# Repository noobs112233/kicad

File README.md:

# Arduino Mega 2560 — KiCad 原理圖繪製練習

對照 `MEGA2560_Rev3e_sch.pdf` 與完整 KiCad 參考專案，使用 **KiCad 9.0** 分工繪製 Arduino Mega 2560 Rev3 原理圖。

---

## Repo 結構

```
kicad/
├── Arduino_Mega2560_Practice/      ← 學生繪製的空白專案（每人畫一個 Section）
│   ├── Arduino_Mega2560_Practice.kicad_pro
│   ├── Arduino_Mega2560_Practice.kicad_sch     (root，4 個子頁框)
│   ├── Section_01_USB_ATmega16U2.kicad_sch     ← 空白
│   ├── Section_02_ATmega2560_MCU.kicad_sch     ← 空白
│   ├── Section_03_Power_Supply.kicad_sch       ← 空白
│   ├── Section_04_Arduino_Headers.kicad_sch    ← 空白
│   ├── Arduino_Mega2560_Lib.kicad_sym          ← 專案符號庫（已預掛 footprint）
│   ├── Arduino_Mega2560_FP.pretty/             ← 自訂 footprint 庫
│   ├── sym-lib-table                           ← 符號庫掛載設定
│   └── fp-lib-table                            ← Footprint 庫掛載設定
│
├── Arduino_Mega2560_Rev3/          ← 完整參考專案（schematic only，無 PCB layout）
│   ├── Arduino Mega 2560.kicad_pro
│   ├── Arduino Mega 2560.kicad_sch             (root)
│   ├── ATMEGA2560-16AU.kicad_sch
│   ├── Power.kicad_sch
│   ├── Headers.kicad_sch
│   ├── Arduino Mega 2560.kicad_sym
│   ├── Arduino Mega 2560.pretty/
│   └── Arduino_Mega2560_Rev3_Schematic.pdf
│
├── PPT/                            ← 課程投影片
├── MEGA2560_Rev3e_sch.pdf          ← 官方參考原理圖
├── arduino_mega2560_BOM.csv        ← 完整 BOM (62 個位號)
└── README.md
```

---

## 分工架構

原理圖分為 **4 個子頁面**，每人負責一個區塊：

| 頁面 | 檔案 | 負責內容 |
|------|------|---------|
| Page 2 | `Section_01_USB_ATmega16U2.kicad_sch` | USB-C 接頭、ESD 保護、ATmega16U2 USB Bridge、晶振 Y2 |
| Page 3 | `Section_02_ATmega2560_MCU.kicad_sch` | ATmega2560 主控 MCU、去耦電容、Reset 電路、晶振 Y1 |
| Page 4 | `Section_03_Power_Supply.kicad_sch` | DC 電源座、NCP1117 5V、LP2985 3.3V、PMOS、LMV358 |
| Page 5 | `Section_04_Arduino_Headers.kicad_sch` | 所有 Arduino 腳位排針（數位/類比/電源） |

---

## 開啟專案

1. 啟動 **KiCad 9.0**
2. `File > Open Project`
3. 選 `Arduino_Mega2560_Practice/Arduino_Mega2560_Practice.kicad_pro`
4. 從 Project Manager 雙擊原理圖開啟 Eeschema
5. 在頁面選擇器切到你負責的 Section 開始繪製

---

## 符號庫 / Footprint 庫使用

### 自動掛載（已設定好，**不需要手動加**）

專案內附的 `sym-lib-table` 與 `fp-lib-table` 已經用 `${KIPRJMOD}` 路徑指向專案資料夾，**只要從 `.kicad_pro` 開啟專案就會自動載入**：

| Library 類型 | 名稱 | 路徑 | 內容 |
|------|------|------|------|
| 符號庫 (Symbol) | `Arduino_Mega2560_Lib` | `Arduino_Mega2560_Lib.kicad_sym` | 92 個符號（ATmega2560、ATmega16U2、被動元件、連接器…） |
| Footprint 庫 | `Arduino_Mega2560_FP` | `Arduino_Mega2560_FP.pretty/` | 4 個自訂 footprint（電源座、針腳、按鍵、Polyfuse） |

> 每個符號已預先連結對應 footprint，**畫原理圖時不需要再指定 footprint**。

### 放置元件

- **Eeschema (原理圖)**: `Place > Add Symbol` (快捷鍵 `A`) → 在 Filter 輸入 `Arduino_Mega2560_Lib:` → 選元件
- **Pcbnew (Footprint)**: `Place > Add Footprint` (快捷鍵 `A`) → Filter 輸入 `Arduino_Mega2560_FP:`

### 看不到符號庫怎麼辦？

如果 Eeschema 找不到 `Arduino_Mega2560_Lib`：

1. `Preferences > Manage Symbol Libraries`
2. 切到 **Project Specific Libraries** 頁籤
3. 確認有一筆 `Arduino_Mega2560_Lib` 指向 `${KIPRJMOD}/Arduino_Mega2560_Lib.kicad_sym`
4. 若無，按 `+` 新增；如果路徑紅字，KiCad 沒讀到專案 → 確認你是用 `.kicad_pro` 開啟，不要直接開 `.kicad_sch`

Footprint 庫同理：`Preferences > Manage Footprint Libraries > Project Specific Libraries`。

---

## 完整參考原理圖

需要對照已完成的版本時，開 `Arduino_Mega2560_Rev3/Arduino Mega 2560.kicad_pro`，含完整 4 頁 schematic。
**此參考專案不附 PCB layout** — layout 要自己畫。

或直接看 PDF：`Arduino_Mega2560_Rev3/Arduino_Mega2560_Rev3_Schematic.pdf`、`MEGA2560_Rev3e_sch.pdf`。

---

## BOM

`arduino_mega2560_BOM.csv` 列出 62 個位號（Reference / Value / Description / Footprint），可以對照確認元件數量與規格。

---

## BOM ↔ 符號庫 對照表

> ⚠️ 符號庫的命名不統一 — 有些用「料號」(`ATmega2560_16AU`)、有些用「通用封裝名」(`Fuse_1812`、`C_SMD_0603`)。直接搜料號常常找不到，請對照下表搜尋：

### 被動元件
| BOM Ref | 元件 | **在符號庫搜這個名字** |
|---|---|---|
| C1–C16 | 0603 SMD 電容 | `C_SMD_0603` |
| PC1, PC2 | 47µF 鋁電解 (THT) | `C_Pol` |
| R1, R2 | 0603 SMD 電阻 | `R_SMD_0603` |
| RN1–RN5 | SIP8 排阻 | `RArray_4x0612` |
| L1 | Ferrite bead 0805 | `FerriteBead_0805` |
| **F1** | **PPTC182LFBN-RC Polyfuse 1812** | **`Fuse_1812`** ← 不是料號！ |

### 主動元件
| BOM Ref | 元件 | **搜這個名字** |
|---|---|---|
| IC1 | LD1117 5V LDO (SOT-223) | `NCP1117_5_0_SOT223` ⚠️ 符號名是 NCP1117，pin out 相容 |
| IC3 | ATmega2560 | `ATmega2560_16AU` |
| IC4 | ATmega16U2 | `ATmega16U2_MU` |
| IC6 | LP2985 3.3V LDO | `LP2985_3_3` |
| IC7 | LMV358 op-amp | `LMV358` |
| T1 | PMV48XP P-MOSFET | `Q_PMOS_GSD` |
| D1 | M7 整流二極體 (SMB) | `D_SMB` |
| D2, D3 | CD1206 高速二極體 | `D_1206` |
| Z1, Z2 | 0603 ESD Varistor | `Varistor_0603` |

### 振盪器 / 開關 / LED
| BOM Ref | 元件 | **搜這個名字** |
|---|---|---|
| Y1 | CSTCE16M0V53-R0 三腳陶瓷諧振器 | `Resonator_3Pin` |
| Y2 | 16MHz HC-49/S 晶振 | `Crystal_HC49` |
| RESET | TS42 Tactile 按鍵 | `SW_Reset` |
| ON / L / RX / TX | 0805 LED | `LED_0805` |

### 連接器
| BOM Ref | 元件 | **搜這個名字** |
|---|---|---|
| X1 | DC 電源座 2.1mm | `Barrel_Jack_Switch` |
| X2 | USB Type-B (BOM) ※ 符號庫實作為 USB-C | `USB_C_16P` ⚠️ 與 BOM 不一致，依 Rev3e 改為 USB-C |
| ICSP, ICSP1 | 2x3 排針 | `Header_2x03` |
| JP5 | 2x2 排針 | `Header_2x02` |
| JP6 | 1x10 排母 | `Conn_01x10` |
| POWER, ADCH, ADCL, COMMUNICATION, PWML | 1x8 排母 | `Conn_01x08` |
| XIO | 2x18 排母 | `Conn_02x18_Odd_Even` |

### 雜項
| BOM Ref | 元件 | **搜這個名字** |
|---|---|---|
| GROUND, RESET-EN | Solder jumper | `SolderJumper_2` |
| FD1–FD4 | Fiducial | `Fiducial_1mm` |

### 電源符號（不在 BOM，畫線時需要）
| 用途 | 名稱 |
|---|---|
| 5V 電源 | `PWR_5V` |
| 3.3V 電源 | `PWR_3V3` |
| GND | `PWR_GND` |
| VCC（USB 5V） | `VCC` |

### 搜尋技巧
1. 在 Eeschema 按 `A` 開啟 Add Symbol
2. 上方 Filter 輸入 `Arduino_Mega2560_Lib:` 只看本專案符號庫（共 31 個符號）
3. 從上表查到名字後直接搜（例如要 Polyfuse 就搜 `Fuse_1812`）

---

## Git 協作流程

### 初始設定

```bash
# 1. 先 fork 這個 repo 到你們組的帳號
# 2. Clone 到本機
git clone https://github.com/<你的組別>/kicad.git
cd kicad
```

### 每個人的工作流程

```bash
# 建立自己的 branch（以你負責的區塊命名）
git checkout -b section/01-usb-atmega16u2   # 依你的區塊修改

# 繪製原理圖後，只 commit 你負責的那個 .kicad_sch 檔
git add Arduino_Mega2560_Practice/Section_01_USB_ATmega16U2.kicad_sch
git commit -m "feat: complete USB ATmega16U2 section schematic"

# Push 到遠端
git push origin section/01-usb-atmega16u2

# 在 GitHub 發 Pull Request 給你們組的 main branch
```

### 合併注意事項

- 每個人只修改**自己負責的 `.kicad_sch` 檔**，不要動到其他人的檔案
- Root 主頁面 `Arduino_Mega2560_Practice.kicad_sch` 只有 4 個方框，不需要修改
- **不要 commit `.kicad_pcb`**（已被 `.gitignore` 排除），這個練習只做原理圖
- `*.bak`、`*.kicad_prl`、`*-backups/` 也都已被 ignore
- 合併後在 KiCad 開 `Arduino_Mega2560_Practice.kicad_pro` 即可看到完整原理圖

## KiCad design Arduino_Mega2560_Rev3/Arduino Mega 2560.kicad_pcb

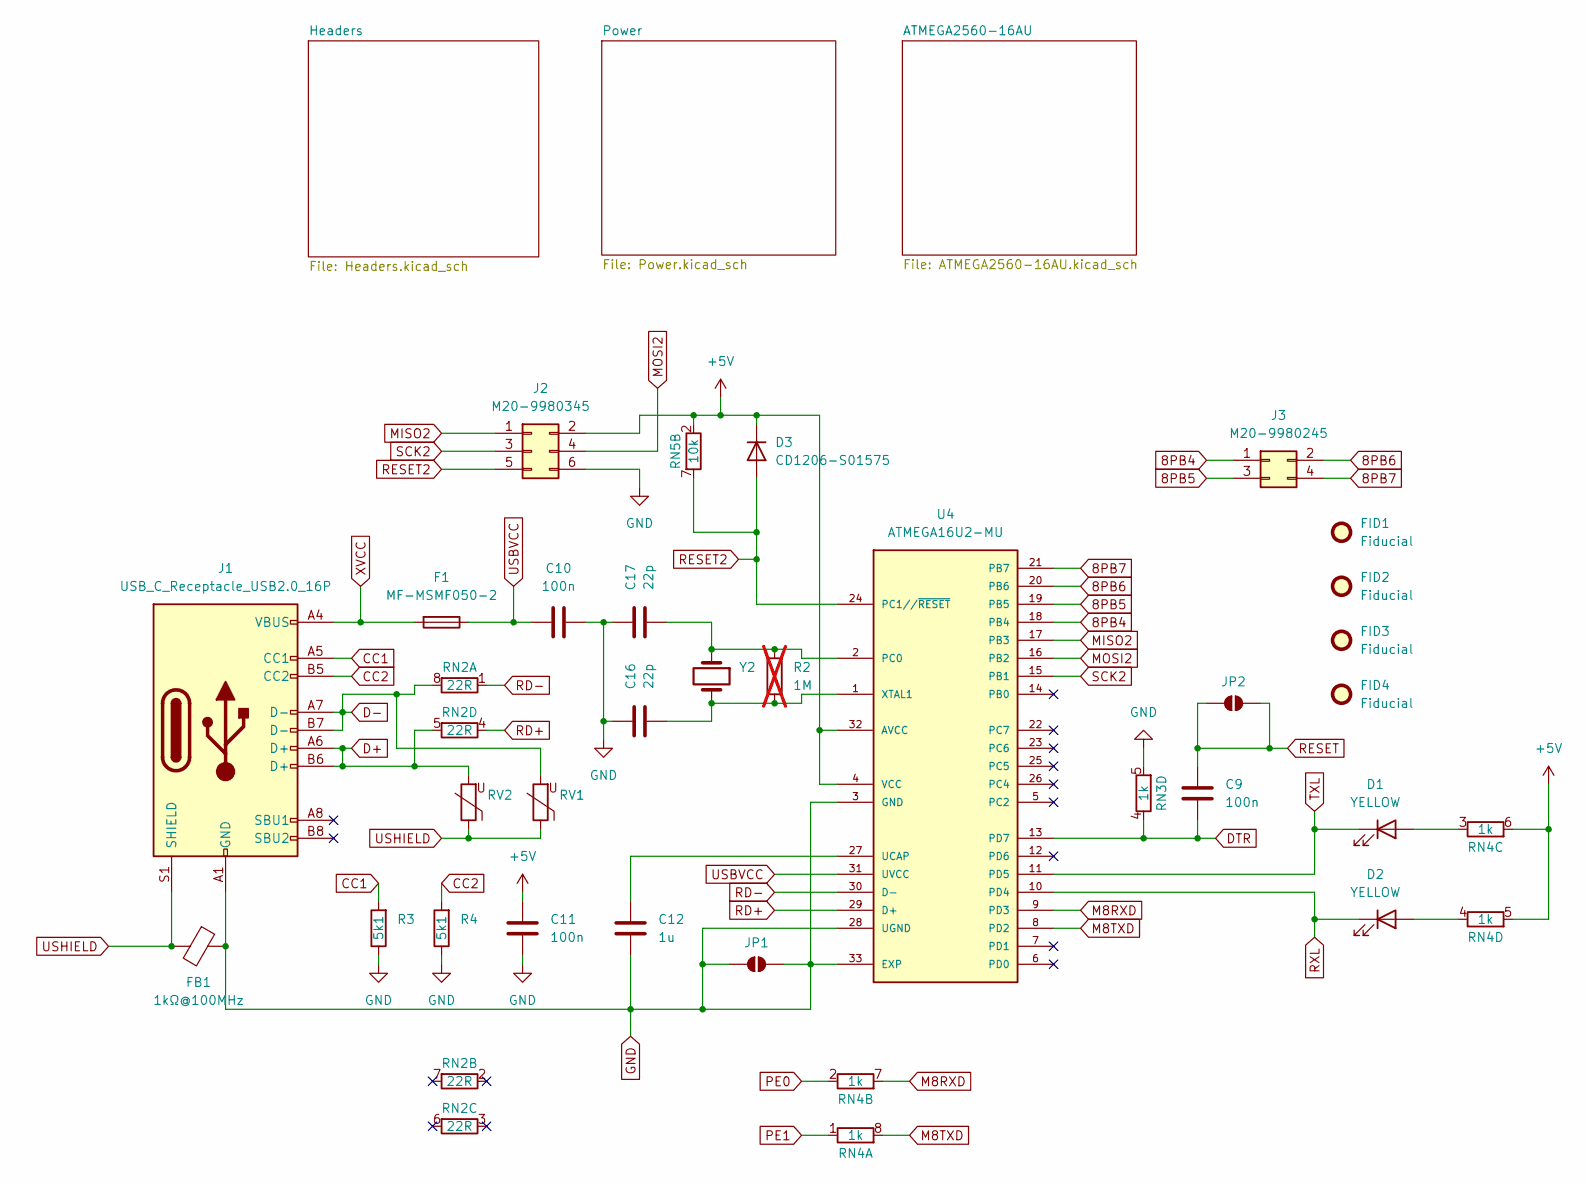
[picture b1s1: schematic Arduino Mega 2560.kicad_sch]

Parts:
C9, C10, C11: 100n; C_0603_1608Metric
C12: 1u; C_0603_1608Metric
C16, C17: 22p; C_0603_1608Metric
D1, D2: YELLOW; LED_0805_2012Metric
D3: CD1206-S01575; D_1206_3216Metric
F1: MF-MSMF050-2; Fuse_1812_4532Metric_Pad1.30x3.40mm_HandSolder
FB1: 1kΩ@100MHz; L_0805_2012Metric
FID1, FID2, FID3, FID4: Fiducial; Fiducial_1mm_Mask3mm
J1: USB_C_Receptacle_USB2.0_16P; USB_C_Receptacle_GCT_USB4105-xx-A_16P_TopMnt_Horizontal
J2: M20-9980345; PinHeader_2x03_P2.54mm_Vertical
J3: M20-9980245; CONN_M20-9980245_HRW
JP1, JP2: SolderJumper_2_Open; SolderJumper-2_P1.3mm_Open_Pad1.0x1.5mm
R2: 1M; R_0603_1608Metric; not fitted
R3, R4: 5k1; R_0603_1608Metric
RN2: 22R; R_Array_Convex_4x0612
RN3, RN4: 1k; R_Array_Convex_4x0612
RN5: 10k; R_Array_Convex_4x0612
RV1, RV2: 5pF@1MHz; R_0603_1608Metric
U4: ATMEGA16U2-MU; VQFN-32-1EP_5x5mm_P0.5mm_EP3.1x3.1mm
Y2: LFXTAL003240BULK; Crystal_HC49-4H_Vertical

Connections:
8PB4: J3.1, U4.18 (PB4)
8PB5: J3.3, U4.19 (PB5)
8PB6: J3.2, U4.20 (PB6)
8PB7: J3.4, U4.21 (PB7)
+5V: C11.1, D3.1 (K), J2.2, RN4.5 (R4.2), RN4.6 (R3.2), RN5.2 (R2.1), U4.4 (VCC), U4.32 (AVCC); also elsewhere on the board
CC1: J1.A5 (CC1), R3.2
CC2: J1.B5 (CC2), R4.2
D+: J1.A6 (D+), J1.B6 (D+), RN2.5 (R4.2), RV2.2
D-: J1.A7 (D-), J1.B7 (D-), RN2.8 (R1.2), RV1.2
DTR: C9.1, RN3.4 (R4.1), U4.13 (PD7)
GND: C10.2, C11.2, C12.2, C16.2, C17.2, FB1.1, J1.A1 (GND), J1.A12 (GND), J1.B1 (GND), J1.B12 (GND), J2.6, JP1.1 (A), JP1.2 (B), R3.1, R4.1, RN3.5 (R4.2), U4.3 (GND), U4.28 (UGND), U4.33 (EXP); also elsewhere on the board
M8RXD: RN4.7 (R2.2), U4.9 (PD3)
M8TXD: RN4.8 (R1.2), U4.8 (PD2)
MISO2: J2.1, U4.17 (PB3)
MOSI2: J2.4, U4.16 (PB2)
unnamed: D1.2 (A), RN4.3 (R3.1)
unnamed: D2.2 (A), RN4.4 (R4.1)
unnamed: C17.1, R2.2, U4.2 (PC0), Y2.1
unnamed: C12.1, U4.27 (UCAP)
unnamed: C16.1, R2.1, U4.1 (XTAL1), Y2.2
PE0: RN4.2 (R2.1); also elsewhere on the board
PE1: RN4.1 (R1.1); also elsewhere on the board
RD+: RN2.4 (R4.1), U4.29 (D+)
RD-: RN2.1 (R1.1), U4.30 (D-)
RESET: C9.2, JP2.1 (A), JP2.2 (B); also elsewhere on the board
RESET2: D3.2 (A), J2.5, RN5.7 (R2.2), U4.24 (PC1//~RESET)
RXL: D2.1 (K), U4.10 (PD4)
SCK2: J2.3, U4.15 (PB1)
TXL: D1.1 (K), U4.11 (PD5)
USBVCC: C10.1, F1.1, U4.31 (UVCC); also elsewhere on the board
USHIELD: FB1.2, J1.S1 (SHIELD), RV1.1, RV2.1
XVCC: F1.2, J1.A4 (VBUS), J1.A9 (VBUS), J1.B4 (VBUS), J1.B9 (VBUS)

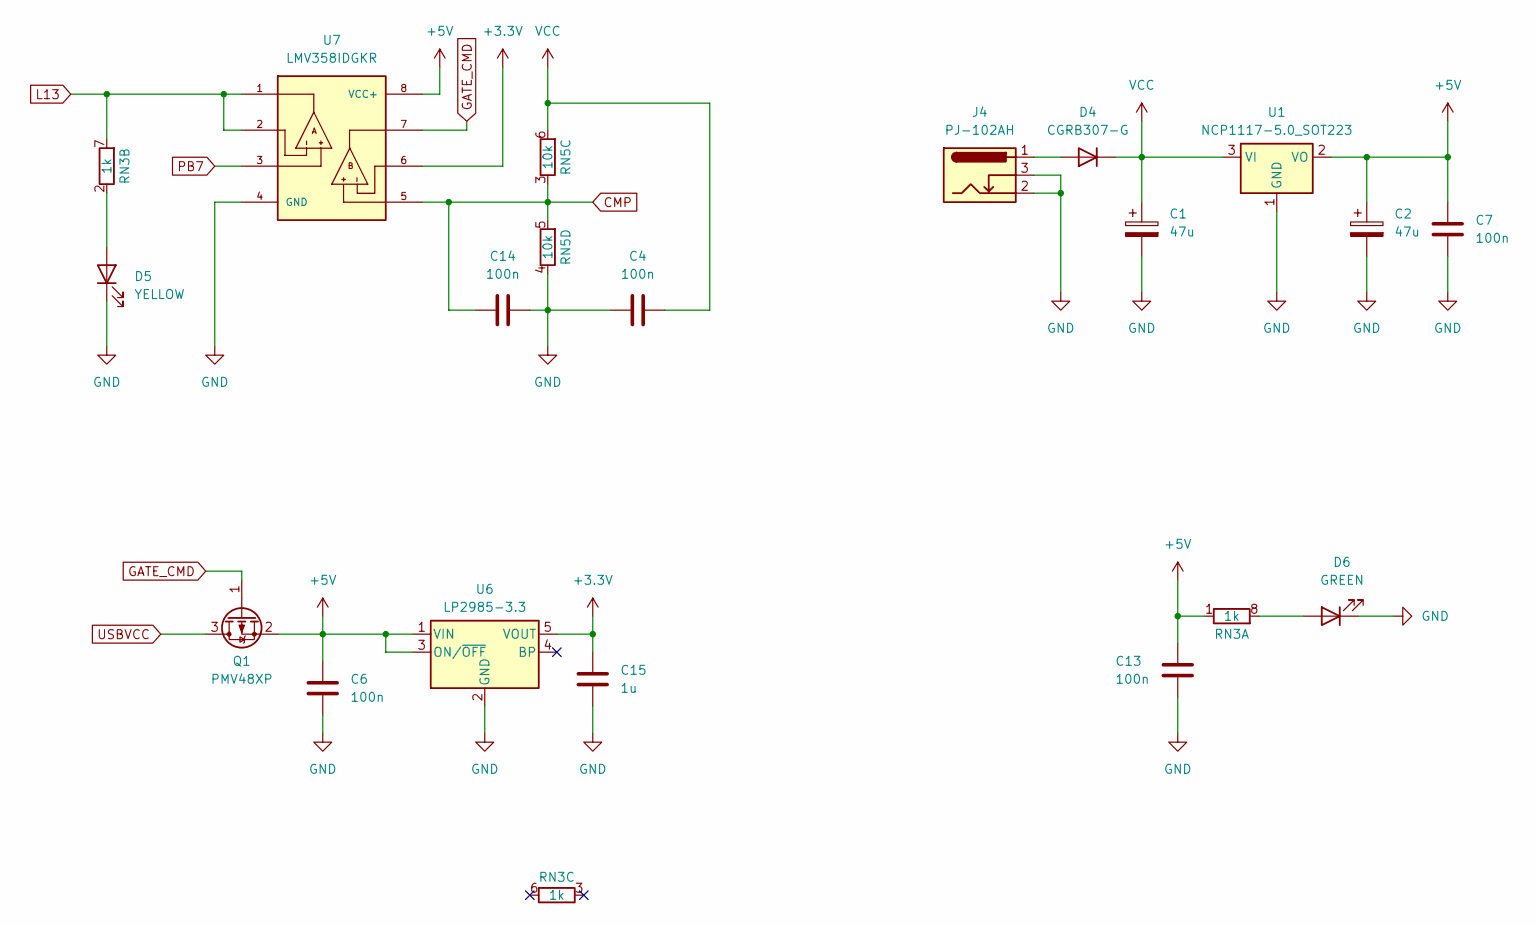
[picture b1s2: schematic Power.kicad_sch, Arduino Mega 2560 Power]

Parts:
C1, C2: 47u; CAP_EEHZA1E470P
C4, C6, C7, C13, C14: 100n; C_0603_1608Metric
C15: 1u; C_0603_1608Metric
D4: CGRB307-G; D_SMB
D5: YELLOW; LED_0805_2012Metric
D6: GREEN; LED_0805_2012Metric
J4: PJ-102AH; BarrelJack_Kycon_KLDX-0202-xC_Horizontal
Q1: PMV48XP; SC-59
RN3: 1k; R_Array_Convex_4x0612
RN5: 10k; R_Array_Convex_4x0612
U1: NCP1117-5.0_SOT223; SOT-223-3_TabPin2
U6: LP2985-3.3; SOT-23-5
U7: LMV358IDGKR; MSOP-8_3x3mm_P0.65mm; PARTREV X

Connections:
+3.3V: C15.2, U6.5 (VOUT), U7.6; also elsewhere on the board
+5V: C2.1, C6.1, C7.1, C13.2, Q1.2 (S), RN3.1 (R1.1), U1.2 (VO), U6.1 (VIN), U6.3 (ON/~OFF), U7.8 (VCC+); also elsewhere on the board
CMP: C14.2, RN5.3 (R3.1), RN5.5 (R4.2), U7.5
GATE_CMD: Q1.1 (G), U7.7
GND: C1.2, C2.2, C4.2, C6.2, C7.2, C13.1, C14.1, C15.1, D5.1 (K), D6.1 (K), J4.2, J4.3, RN5.4 (R4.1), U1.1 (GND), U6.2 (GND), U7.4 (GND); also elsewhere on the board
L13: RN3.7 (R2.2), U7.1, U7.2
unnamed: D4.2 (A), J4.1
unnamed: D5.2 (A), RN3.2 (R2.1)
unnamed: D6.2 (A), RN3.8 (R1.2)
PB7: U7.3; also elsewhere on the board
USBVCC: Q1.3 (D); also elsewhere on the board
VCC: C1.1, C4.1, D4.1 (K), RN5.6 (R3.2), U1.3 (VI); also elsewhere on the board

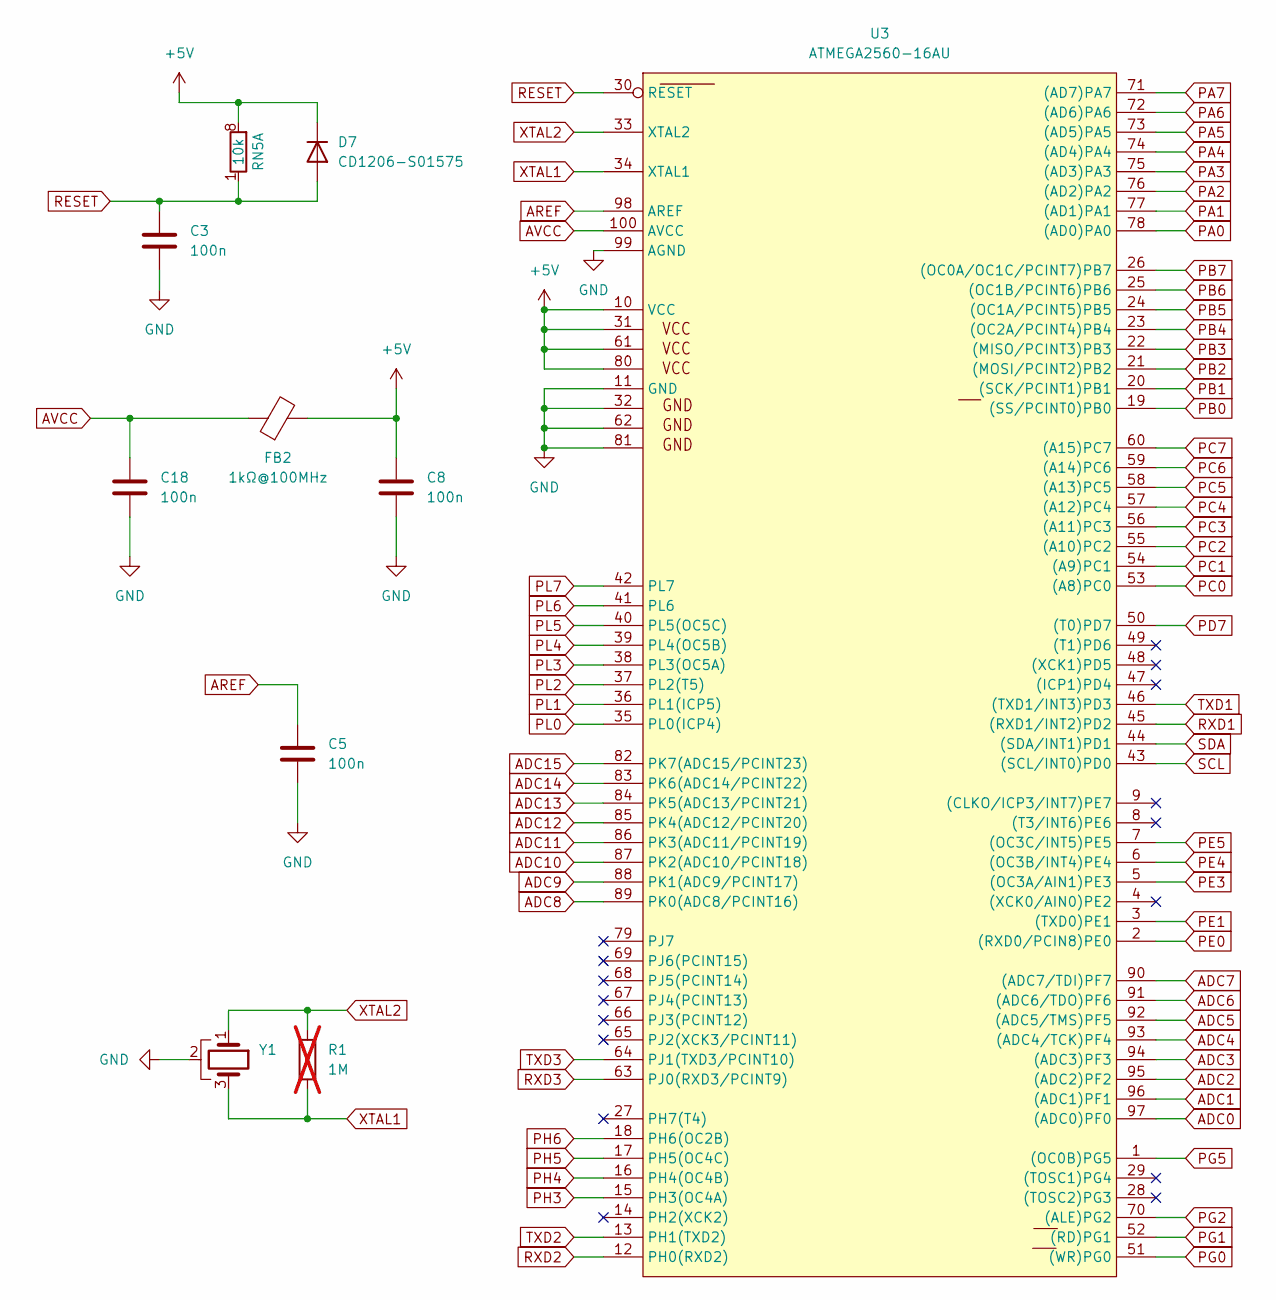
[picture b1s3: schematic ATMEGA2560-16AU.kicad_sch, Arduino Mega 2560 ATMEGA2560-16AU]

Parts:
C3, C5, C8, C18: 100n; C_0603_1608Metric
D7: CD1206-S01575; D_1206_3216Metric
FB2: 1kΩ@100MHz; L_0805_2012Metric
R1: 1M; R_0603_1608Metric; not fitted
RN5: 10k; R_Array_Convex_4x0612
U3: ATMEGA2560-16AU; TQFP-100_14x14mm_P0.5mm
Y1: CSTNE16M0V530000R0; Resonator_SMD_Murata_CSTxExxV-3Pin_3.0x1.1mm

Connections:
+5V: C8.1, D7.1 (K), FB2.2, RN5.8 (R1.2), U3.10 (VCC), U3.31 (VCC1), U3.61 (VCC2), U3.80 (VCC3); also elsewhere on the board
ADC0: U3.97 ((ADC0)PF0); also elsewhere on the board
ADC1: U3.96 ((ADC1)PF1); also elsewhere on the board
ADC2: U3.95 ((ADC2)PF2); also elsewhere on the board
ADC3: U3.94 ((ADC3)PF3); also elsewhere on the board
ADC4: U3.93 ((ADC4/TCK)PF4); also elsewhere on the board
ADC5: U3.92 ((ADC5/TMS)PF5); also elsewhere on the board
ADC6: U3.91 ((ADC6/TDO)PF6); also elsewhere on the board
ADC7: U3.90 ((ADC7/TDI)PF7); also elsewhere on the board
ADC8: U3.89 (PK0(ADC8/PCINT16)); also elsewhere on the board
ADC9: U3.88 (PK1(ADC9/PCINT17)); also elsewhere on the board
ADC10: U3.87 (PK2(ADC10/PCINT18)); also elsewhere on the board
ADC11: U3.86 (PK3(ADC11/PCINT19)); also elsewhere on the board
ADC12: U3.85 (PK4(ADC12/PCINT20)); also elsewhere on the board
ADC13: U3.84 (PK5(ADC13/PCINT21)); also elsewhere on the board
ADC14: U3.83 (PK6(ADC14/PCINT22)); also elsewhere on the board
ADC15: U3.82 (PK7(ADC15/PCINT23)); also elsewhere on the board
AREF: C5.1, U3.98 (AREF); also elsewhere on the board
AVCC: C18.1, FB2.1, U3.100 (AVCC)
GND: C3.2, C5.2, C8.2, C18.2, U3.11 (GND), U3.32 (GND1), U3.62 (GND2), U3.81 (GND3), U3.99 (AGND), Y1.2; also elsewhere on the board
PA0: U3.78 ((AD0)PA0); also elsewhere on the board
PA1: U3.77 ((AD1)PA1); also elsewhere on the board
PA2: U3.76 ((AD2)PA2); also elsewhere on the board
PA3: U3.75 ((AD3)PA3); also elsewhere on the board
PA4: U3.74 ((AD4)PA4); also elsewhere on the board
PA5: U3.73 ((AD5)PA5); also elsewhere on the board
PA6: U3.72 ((AD6)PA6); also elsewhere on the board
PA7: U3.71 ((AD7)PA7); also elsewhere on the board
PB0: U3.19 ((SS/PCINT0)PB0); also elsewhere on the board
PB1: U3.20 ((SCK/PCINT1)PB1); also elsewhere on the board
PB2: U3.21 ((MOSI/PCINT2)PB2); also elsewhere on the board
PB3: U3.22 ((MISO/PCINT3)PB3); also elsewhere on the board
PB4: U3.23 ((OC2A/PCINT4)PB4); also elsewhere on the board
PB5: U3.24 ((OC1A/PCINT5)PB5); also elsewhere on the board
PB6: U3.25 ((OC1B/PCINT6)PB6); also elsewhere on the board
PB7: U3.26 ((OC0A/OC1C/PCINT7)PB7); also elsewhere on the board
PC0: U3.53 ((A8)PC0); also elsewhere on the board
PC1: U3.54 ((A9)PC1); also elsewhere on the board
PC2: U3.55 ((A10)PC2); also elsewhere on the board
PC3: U3.56 ((A11)PC3); also elsewhere on the board
PC4: U3.57 ((A12)PC4); also elsewhere on the board
PC5: U3.58 ((A13)PC5); also elsewhere on the board
PC6: U3.59 ((A14)PC6); also elsewhere on the board
PC7: U3.60 ((A15)PC7); also elsewhere on the board
PD7: U3.50 ((T0)PD7); also elsewhere on the board
PE0: U3.2 ((RXD0/PCIN8)PE0); also elsewhere on the board
PE1: U3.3 ((TXD0)PE1); also elsewhere on the board
PE3: U3.5 ((OC3A/AIN1)PE3); also elsewhere on the board
PE4: U3.6 ((OC3B/INT4)PE4); also elsewhere on the board
PE5: U3.7 ((OC3C/INT5)PE5); also elsewhere on the board
PG0: U3.51 ((WR)PG0); also elsewhere on the board
PG1: U3.52 ((RD)PG1); also elsewhere on the board
PG2: U3.70 ((ALE)PG2); also elsewhere on the board
PG5: U3.1 ((OC0B)PG5); also elsewhere on the board
PH3: U3.15 (PH3(OC4A)); also elsewhere on the board
PH4: U3.16 (PH4(OC4B)); also elsewhere on the board
PH5: U3.17 (PH5(OC4C)); also elsewhere on the board
PH6: U3.18 (PH6(OC2B)); also elsewhere on the board
PL0: U3.35 (PL0(ICP4)); also elsewhere on the board
PL1: U3.36 (PL1(ICP5)); also elsewhere on the board
PL2: U3.37 (PL2(T5)); also elsewhere on the board
PL3: U3.38 (PL3(OC5A)); also elsewhere on the board
PL4: U3.39 (PL4(OC5B)); also elsewhere on the board
PL5: U3.40 (PL5(OC5C)); also elsewhere on the board
PL6: U3.41 (PL6); also elsewhere on the board
PL7: U3.42 (PL7); also elsewhere on the board
RESET: C3.1, D7.2 (A), RN5.1 (R1.1), U3.30 (RESET); also elsewhere on the board
RXD1: U3.45 ((RXD1/INT2)PD2); also elsewhere on the board
RXD2: U3.12 (PH0(RXD2)); also elsewhere on the board
RXD3: U3.63 (PJ0(RXD3/PCINT9)); also elsewhere on the board
SCL: U3.43 ((SCL/INT0)PD0); also elsewhere on the board
SDA: U3.44 ((SDA/INT1)PD1); also elsewhere on the board
TXD1: U3.46 ((TXD1/INT3)PD3); also elsewhere on the board
TXD2: U3.13 (PH1(TXD2)); also elsewhere on the board
TXD3: U3.64 (PJ1(TXD3/PCINT10)); also elsewhere on the board
XTAL1: R1.1, U3.34 (XTAL1), Y1.3
XTAL2: R1.2, U3.33 (XTAL2), Y1.1

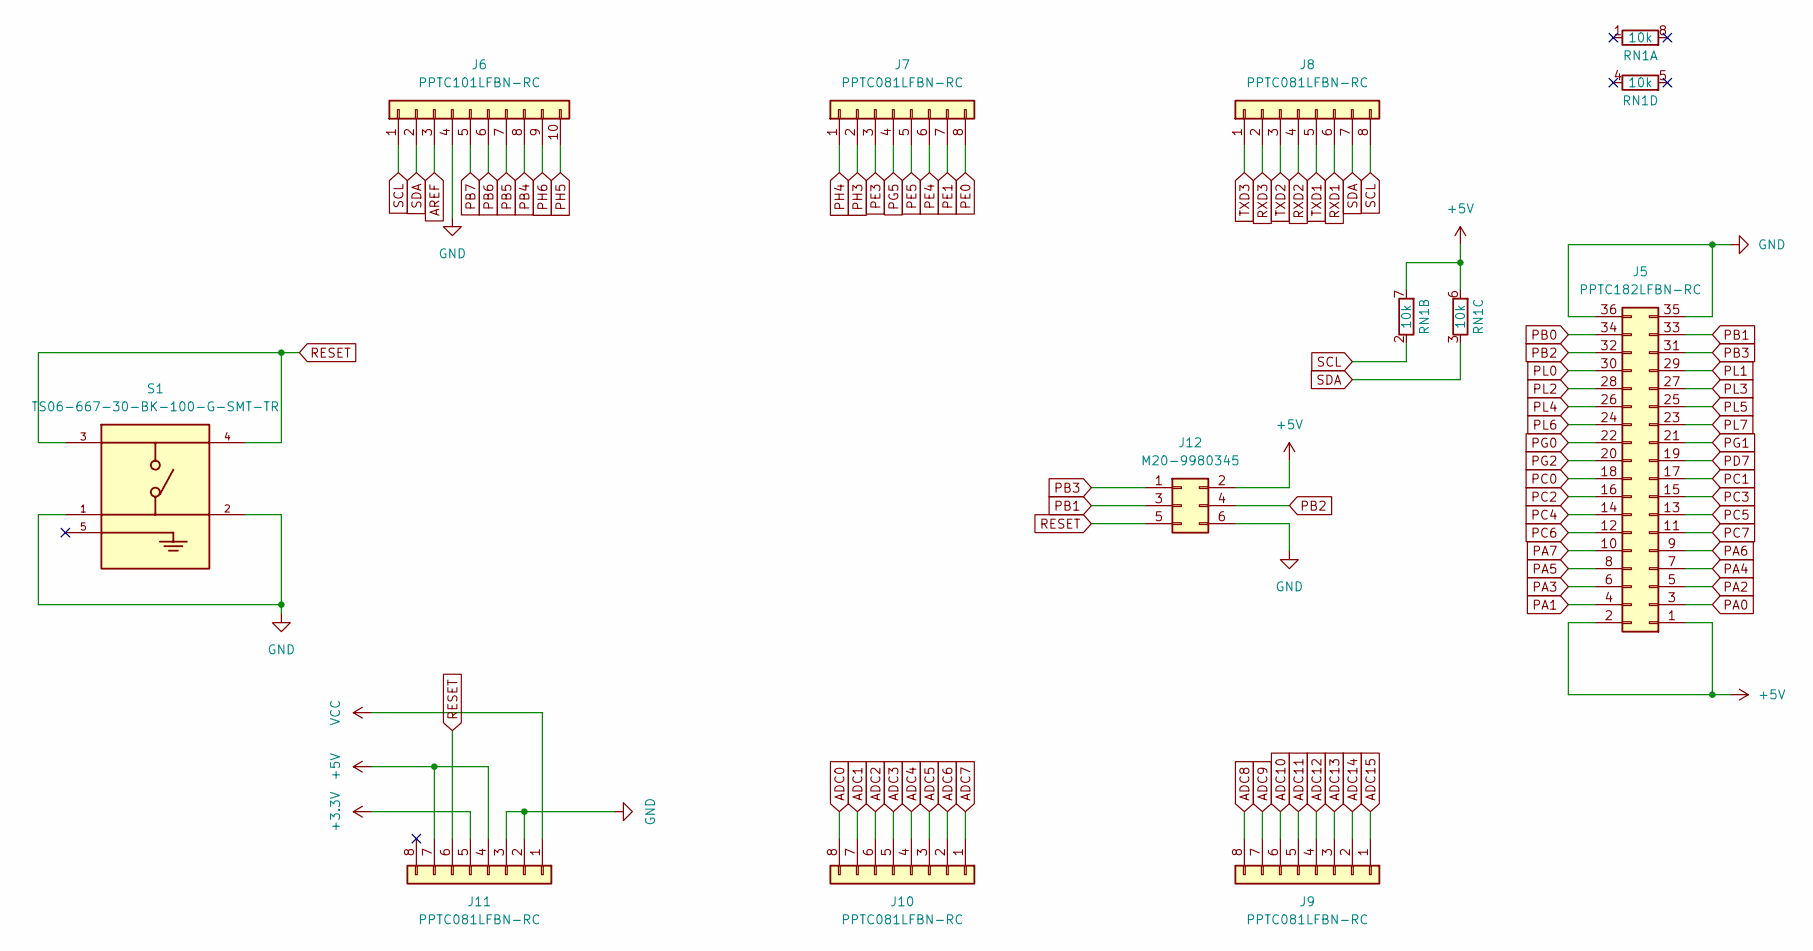
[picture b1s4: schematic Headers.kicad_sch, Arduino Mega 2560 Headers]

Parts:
J5: PPTC182LFBN-RC
J6: PPTC101LFBN-RC; PinSocket_1x10_P2.54mm_Vertical
J7, J8, J9, J10, J11: PPTC081LFBN-RC; PinSocket_1x08_P2.54mm_Vertical
J12: M20-9980345; PinHeader_2x03_P2.54mm_Vertical
RN1: 10k; R_Array_Convex_4x0612
S1: TS06-667-30-BK-100-G-SMT-TR; SW_TS06-667-30-BK-100-G-SMT-TR; PARTREV 1.0

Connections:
+3.3V: J11.5; also elsewhere on the board
+5V: J5.1, J5.2, J11.4, J11.7, J12.2, RN1.6 (R3.2), RN1.7 (R2.2); also elsewhere on the board
ADC0: J10.8; also elsewhere on the board
ADC1: J10.7; also elsewhere on the board
ADC2: J10.6; also elsewhere on the board
ADC3: J10.5; also elsewhere on the board
ADC4: J10.4; also elsewhere on the board
ADC5: J10.3; also elsewhere on the board
ADC6: J10.2; also elsewhere on the board
ADC7: J10.1; also elsewhere on the board
ADC8: J9.8; also elsewhere on the board
ADC9: J9.7; also elsewhere on the board
ADC10: J9.6; also elsewhere on the board
ADC11: J9.5; also elsewhere on the board
ADC12: J9.4; also elsewhere on the board
ADC13: J9.3; also elsewhere on the board
ADC14: J9.2; also elsewhere on the board
ADC15: J9.1; also elsewhere on the board
AREF: J6.3; also elsewhere on the board
GND: J5.35, J5.36, J6.4, J11.2, J11.3, J12.6, S1.1, S1.2; also elsewhere on the board
PA0: J5.3; also elsewhere on the board
PA1: J5.4; also elsewhere on the board
PA2: J5.5; also elsewhere on the board
PA3: J5.6; also elsewhere on the board
PA4: J5.7; also elsewhere on the board
PA5: J5.8; also elsewhere on the board
PA6: J5.9; also elsewhere on the board
PA7: J5.10; also elsewhere on the board
PB0: J5.34; also elsewhere on the board
PB1: J5.33, J12.3; also elsewhere on the board
PB2: J5.32, J12.4; also elsewhere on the board
PB3: J5.31, J12.1; also elsewhere on the board
PB4: J6.8; also elsewhere on the board
PB5: J6.7; also elsewhere on the board
PB6: J6.6; also elsewhere on the board
PB7: J6.5; also elsewhere on the board
PC0: J5.18; also elsewhere on the board
PC1: J5.17; also elsewhere on the board
PC2: J5.16; also elsewhere on the board
PC3: J5.15; also elsewhere on the board
PC4: J5.14; also elsewhere on the board
PC5: J5.13; also elsewhere on the board
PC6: J5.12; also elsewhere on the board
PC7: J5.11; also elsewhere on the board
PD7: J5.19; also elsewhere on the board
PE0: J7.8; also elsewhere on the board
PE1: J7.7; also elsewhere on the board
PE3: J7.3; also elsewhere on the board
PE4: J7.6; also elsewhere on the board
PE5: J7.5; also elsewhere on the board
PG0: J5.22; also elsewhere on the board
PG1: J5.21; also elsewhere on the board
PG2: J5.20; also elsewhere on the board
PG5: J7.4; also elsewhere on the board
PH3: J7.2; also elsewhere on the board
PH4: J7.1; also elsewhere on the board
PH5: J6.10; also elsewhere on the board
PH6: J6.9; also elsewhere on the board
PL0: J5.30; also elsewhere on the board
PL1: J5.29; also elsewhere on the board
PL2: J5.28; also elsewhere on the board
PL3: J5.27; also elsewhere on the board
PL4: J5.26; also elsewhere on the board
PL5: J5.25; also elsewhere on the board
PL6: J5.24; also elsewhere on the board
PL7: J5.23; also elsewhere on the board
RESET: J11.6, J12.5, S1.3, S1.4; also elsewhere on the board
RXD1: J8.6; also elsewhere on the board
RXD2: J8.4; also elsewhere on the board
RXD3: J8.2; also elsewhere on the board
SCL: J6.1, J8.8, RN1.2 (R2.1); also elsewhere on the board
SDA: J6.2, J8.7, RN1.3 (R3.1); also elsewhere on the board
TXD1: J8.5; also elsewhere on the board
TXD2: J8.3; also elsewhere on the board
TXD3: J8.1; also elsewhere on the board
VCC: J11.1; also elsewhere on the board

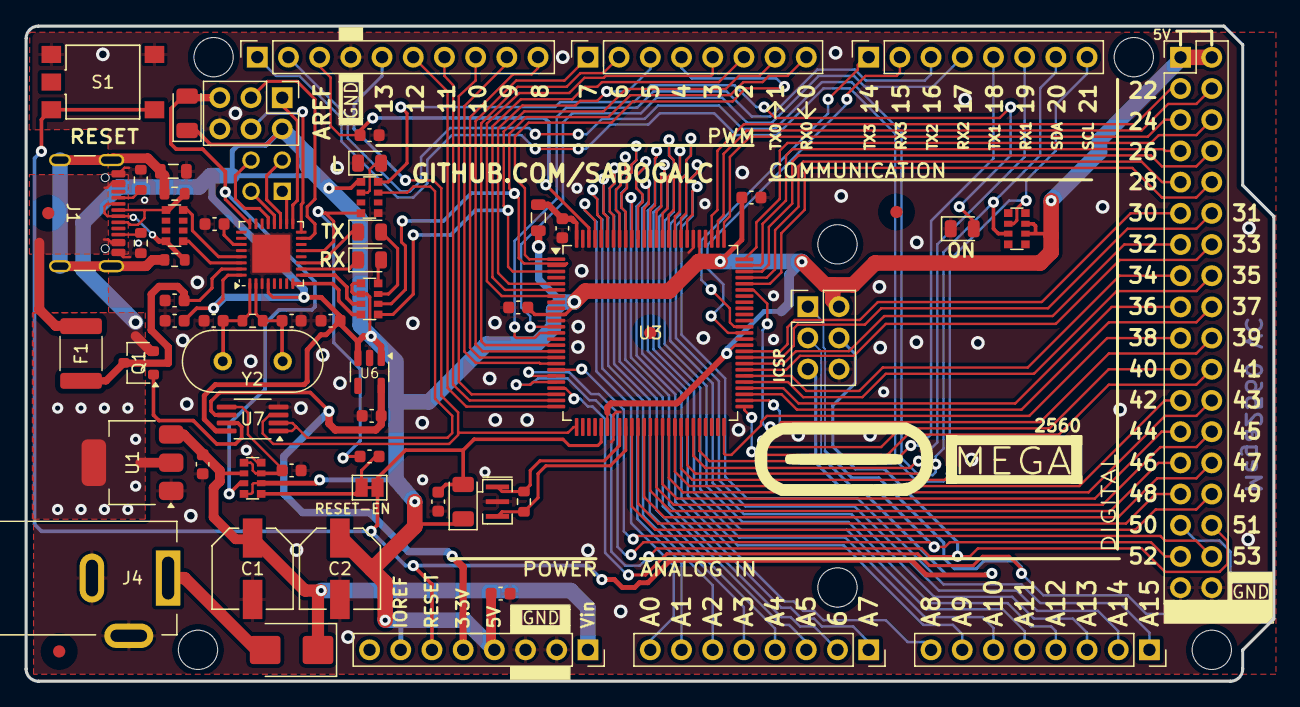
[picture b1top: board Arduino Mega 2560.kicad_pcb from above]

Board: 2 copper layers, 101.6 x 53.3 mm, 66 parts (1 on the bottom side), 112 nets.

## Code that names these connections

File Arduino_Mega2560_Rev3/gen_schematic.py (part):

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Fixed:
  - KiCad 9.0 correct lib_ids (+3.3V, LD1117-5.0, BarrelJack, etc.)
  - No overlaps: A0 paper (1189x841mm), sections well-separated
  - Custom power nets → global_label (USBVCC, VIN, PWRIN, VBUS)
  - Fiducials removed (PCB-only, no schematic symbol in KiCad 9.0)
"""
import uuid as _uuid
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     "Package_QFP:TQFP-100_14x14mm_P0.8mm", IC3X, IC3Y)

# ── IC3 Power (top pins) ──────────────────────────────────────────────────────
# Multiple VCC pins at top of symbol (pins 7,11,62,65,93=AVCC)
for dx in [-7.62,-5.08,-2.54,0,2.54,5.08]:
    pwr("+5V", IC3X+dx, IC3T-6)
    wire(IC3X+dx, IC3T-6, IC3X+dx, IC3T)
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
# ── IC3 LEFT SIDE PINS ────────────────────────────────────────────────────────
# PB port (D10-D13, SPI, D50-D53)
#   PB0(SS)=D53, PB1(SCK)=D52, PB2(MOSI)=D51, PB3(MISO)=D50
#   PB4(OC2A)=D10, PB5(OC1A)=D11, PB6(OC1B)=D12, PB7(OC0A)=D13
for net,dy in [("D53",-9*1.27),("D52",-8*1.27),("D51",-7*1.27),("D50",-6*1.27),
               ("D10",-5*1.27),("D11",-4*1.27),("D12",-3*1.27),("D13",-2*1.27)]:
    lbl(net, IC3L-5, IC3Y+dy, just="right")
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pwr("+5V",122,PS_Y-5); wire(122,PS_Y-2,122,PS_Y-5)
pwr("GND",115,PS_Y+5); wire(115,PS_Y+2,115,PS_Y+5)

# PC1, PC2: 47uF bulk caps
comp("Device:CP","PC1","47uF","Capacitor_THT:CP_Radial_D6.3mm_P2.50mm",138,PS_Y-2)
comp("Device:CP","PC2","47uF","Capacitor_THT:CP_Radial_D6.3mm_P2.50mm",152,PS_Y-2)
for cx in [138,152]:
    pwr("+5V",cx,PS_Y-8); pwr("GND",cx,PS_Y+5)
    wire(cx,PS_Y-8,cx,PS_Y-5); wire(cx,PS_Y+2,cx,PS_Y+5)
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
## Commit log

2026-04-17 upload
2026-04-17 docs: add BOM-to-symbol cross-reference table
2026-05-08 爽啦HEHE
2026-05-08 Revert "爽啦HEHE"
    This reverts commit 424b3fbb69cbc3a69e98a571511e804e9fc963c3.
2026-05-10 USB完成
2026-05-10 USB完成2
2026-05-22 0522
